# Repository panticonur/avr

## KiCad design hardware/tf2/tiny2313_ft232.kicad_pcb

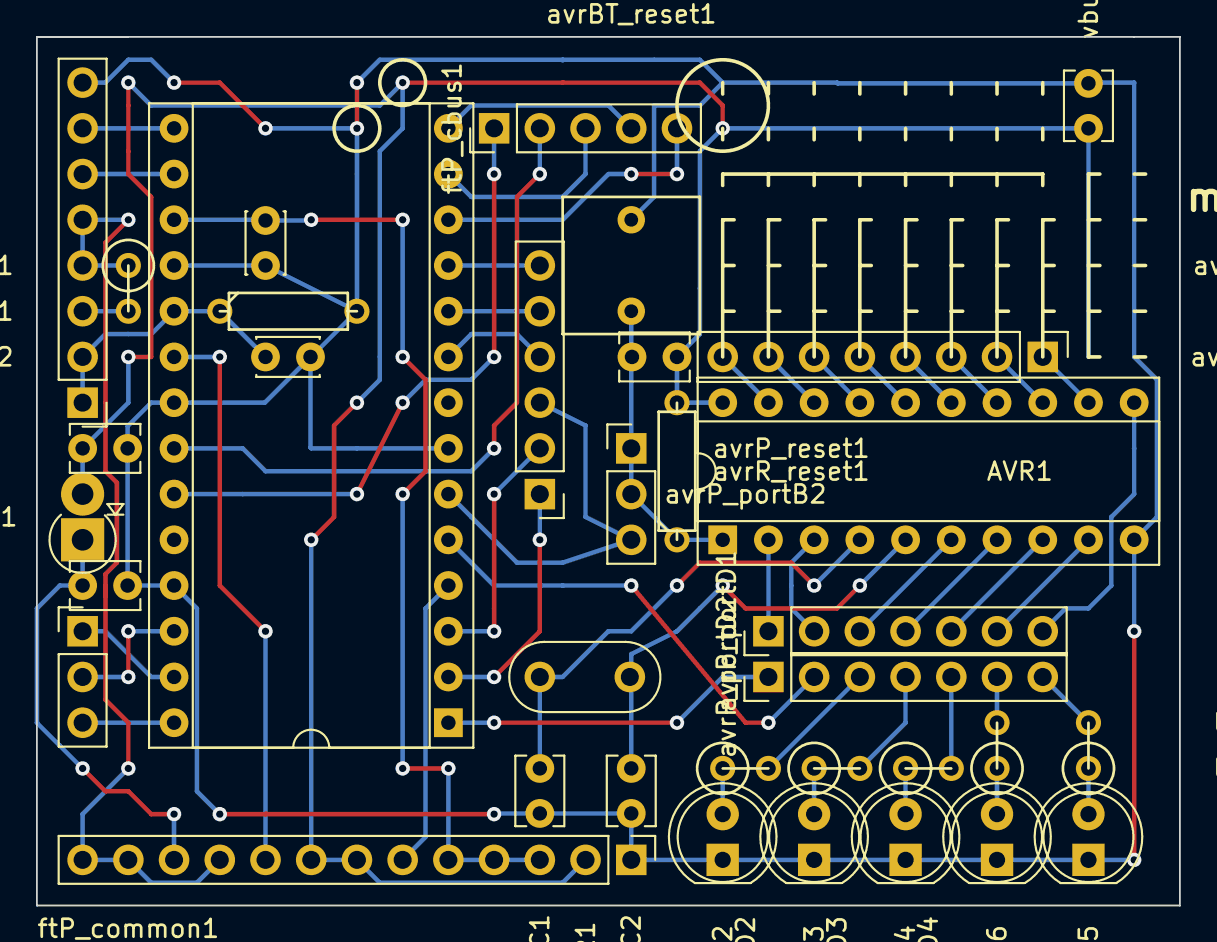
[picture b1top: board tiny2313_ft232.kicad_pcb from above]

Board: 2 copper layers, 63.5 x 48.3 mm, 35 parts (0 on the bottom side), 55 nets.

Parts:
AVR1: ATTINY2313-20PU; DIP-20_W7.62mm_Socket
FT1: FT232RL_pnt; DIP-28_W15.24mm_Socket
avrBT_reset1: Button; push_button
avrC_reset1: 100n; C_Disc_D3.8mm_W2.6mm_P2.50mm
avrP_portB1: CONN_01X08; Pin_Header_Straight_1x08_Pitch2.54mm
avrP_portB2: CONN_01X06; Pin_Header_Straight_1x06_Pitch2.54mm
avrP_portD1, avrP_portD2: CONN_01X07; Pin_Header_Straight_1x07_Pitch2.54mm
avrP_reset1: CONN_01X05; Pin_Header_Straight_1x03_Pitch2.54mm
avrR_reset1: 10k; R3
ftC1_33: 100n; C_Disc_D3.4mm_W2.1mm_P2.50mm
ftC_reset1: 100n; C_Disc_D3.4mm_W2.1mm_P2.50mm
ftP_cbus1: CONN_01X05; Pin_Header_Straight_1x05_Pitch2.54mm
ftP_common1: CONN_01X13; Pin_Header_Straight_1x13_Pitch2.54mm
ftP_quartz1: CONN_01X03; Pin_Header_Straight_1x03_Pitch2.54mm
ftP_usb1: CONN_01X08; Pin_Header_Straight_1x08_Pitch2.54mm
ftR_reset1: 4.7k; R1
ftR_reset2: 10k; R3
ledR_portD2: 2K; R1
ledR_portD3: 3k; R1
ledR_portD4: 1.5k; R1
ledR_portD5: 1k; R1
ledR_portD6: 180; R1
led_portD2: white; LED_D5.0mm
led_portD3: blue; LED_D5.0mm
led_portD4: red; LED_D5.0mm
led_portD5: yellow; LED_D5.0mm
led_portD6: green; LED_D5.0mm
quartzAVR1: Crystal; Resonator-2pin_w8.0mm_h3.5mm
quartzC1, quartzC2: 22n; C_Disc_D3.8mm_W2.6mm_P2.50mm
vbusBead1: Ferrite_Bead; D_DO-15_P2.54mm_Vertical_AnodeUp
vbusC1: 15n; C_Disc_D3.8mm_W2.6mm_P2.50mm
vbusC2: 100n; C_Disc_D3.8mm_W2.6mm_P2.50mm
vbusC3: 47u; C_Disc_D3.8mm_W2.6mm_P2.50mm

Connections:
+3V3: FT1.17, ftC1_33.2, ftP_common1.3, ftP_common1.4, ftP_common1.5
+5V: ftP_common1.10, ftP_common1.12, ftP_common1.13, ftP_usb1.4, ftP_usb1.5, ftR_reset1.1
/DTR: FT1.2, avrP_portB2.1
/MISO: FT1.11, avrP_portB2.6
/MOSI: FT1.10, avrP_portB2.5
/PA0: AVR1.5, quartzAVR1.2, quartzC2.1
/PA1: AVR1.4, quartzAVR1.1, quartzC1.1
/PB0: AVR1.12, avrP_portB1.1
/PB1: AVR1.13, avrP_portB1.2
/PB2: AVR1.14, avrP_portB1.3
/PB3: AVR1.15, avrP_portB1.4
/PB4: AVR1.16, avrP_portB1.5
/PB5-MOSI: AVR1.17, avrP_portB1.6
/PB6-MISO: AVR1.18, avrP_portB1.7
/PB7-SCK: AVR1.19, avrP_portB1.8
/PD0: AVR1.2, avrP_portD1.1
/PD1: AVR1.3, avrP_portD1.2
/PD2: AVR1.6, avrP_portD1.3
/PD3: AVR1.7, avrP_portD1.4
/PD4: AVR1.8, avrP_portD1.5
/PD5: AVR1.9, avrP_portD1.6
/PD6: AVR1.11, avrP_portD1.7
/PWREN: FT1.14, ftP_cbus1.4
/RTS: FT1.3, avrP_portB2.2
/RXD: FT1.1, avrP_portD2.1
/RXLED: FT1.22, ftP_cbus1.2
/SCK: FT1.9, avrP_portB2.4
/SLEEP: FT1.12, ftP_cbus1.5
/TXD: FT1.5, avrP_portD2.2
/TXDEN: FT1.13, ftP_cbus1.3
/TXLED: FT1.23, ftP_cbus1.1
/VCC: AVR1.20, avrC_reset1.1, avrR_reset1.2, ftP_common1.2, ftP_common1.7, ftP_common1.8, vbusBead1.2, vbusC2.1, vbusC3.1
/VCCIO: FT1.4, ftP_common1.6
/VCC_FT: FT1.20, ftP_common1.9
/VCC_filter: ftP_common1.11, vbusBead1.1, vbusC1.1
/blue: avrP_portD2.4, ledR_portD3.2
/ft_reset: FT1.19, ftC_reset1.1, ftP_usb1.1, ftP_usb1.2, ftR_reset2.1
/green: avrP_portD2.6, ledR_portD6.2
/red: avrP_portD2.5, ledR_portD4.2
/reset: AVR1.1, avrBT_reset1.2, avrC_reset1.2, avrP_reset1.1, avrP_reset1.2, avrR_reset1.1
/resumePC: FT1.6, avrP_portB2.3, avrP_reset1.3
/usb+: FT1.15, ftP_usb1.7
/usb-: FT1.16, ftP_usb1.6
/white: avrP_portD2.3, ledR_portD2.2
/yellow: avrP_portD2.7, ledR_portD5.2
GND: AVR1.10, FT1.7, FT1.18, FT1.21, FT1.25, avrBT_reset1.1, ftC1_33.1, ftC_reset1.2, ftP_common1.1, ftP_usb1.8, ftR_reset2.2, led_portD2.1, led_portD3.1, led_portD4.1, led_portD5.1, led_portD6.1, quartzC1.2, quartzC2.2, vbusC1.2, vbusC2.2, vbusC3.2
unnamed: FT1.26, ftP_quartz1.2
unnamed: FT1.27, ftP_quartz1.1
unnamed: FT1.28, ftP_quartz1.3
unnamed: ftP_usb1.3, ftR_reset1.2
unnamed: ledR_portD2.1, led_portD2.2
unnamed: ledR_portD3.1, led_portD3.2
unnamed: ledR_portD4.1, led_portD4.2
unnamed: ledR_portD5.1, led_portD5.2
unnamed: ledR_portD6.1, led_portD6.2

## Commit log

2018-03-12 add hardware
2018-03-12 tf2 bugfix
2018-03-17 add host library template driver and python example
2018-03-22 avrdude
2018-03-22 gitignore
2018-03-30 update attiny2313 lib
2018-04-05 add app_template
2018-04-06 update ft_utils & makefile
2018-04-08 app_template Windows port
2018-04-13 update misc
2018-04-17 footprints
2018-06-01 update soft
2022-07-24 test
